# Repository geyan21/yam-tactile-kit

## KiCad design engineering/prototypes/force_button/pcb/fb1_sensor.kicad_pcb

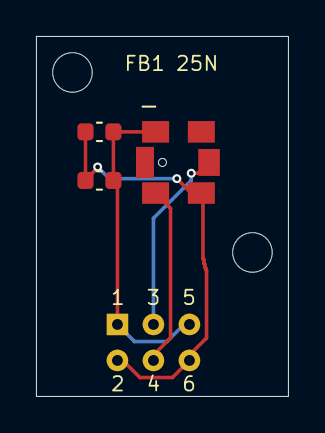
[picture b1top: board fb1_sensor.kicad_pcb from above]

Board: 2 copper layers, 14.0 x 20.0 mm, 6 parts (0 on the bottom side), 4 nets.

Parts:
C1: 100nF 16V X7R; C1
C2: 1uF 16V X7R; effective capacitance to be verified; C2
H1, H2: M2 clearance; MOUNT_M2
JW: Six separate soldered cable conductors; JW
U1: FMAMSDXX025WC2C3; U1

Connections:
GND_REMOTE: C1.2, C2.2, JW.2, JW.6, U1.3
SCL: JW.4, U1.4
SDA: JW.3, U1.5
VDD_REMOTE: C1.1, C2.1, JW.1, JW.5, U1.1

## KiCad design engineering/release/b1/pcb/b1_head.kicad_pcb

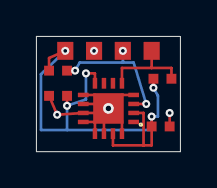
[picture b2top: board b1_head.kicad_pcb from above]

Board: 2 copper layers, 8.0 x 6.4 mm, 6 parts (0 on the bottom side), 4 nets.

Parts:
C1: 100nF 16V X7R 0402; C1
C2: 100nF 16V X7R 0402; C2
J1: Solder wires 3V3 GND SCL SDA; J1
R1: 10k 1% 0402; R1
R2: 10k 1% 0402; R2
U1: MLX90393SLW-ABA-011; U1

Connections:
3V3: C1.1, C2.2, J1.1, R1.1, R2.1, U1.2, U1.8, U1.15
GND: C1.2, C2.1, J1.2, U1.4, U1.9, U1.10, U1.11, U1.12, U1.13, U1.14, U1.16, U1.17
SCL: J1.3, R1.2, U1.3
SDA: J1.4, R2.2, U1.5
